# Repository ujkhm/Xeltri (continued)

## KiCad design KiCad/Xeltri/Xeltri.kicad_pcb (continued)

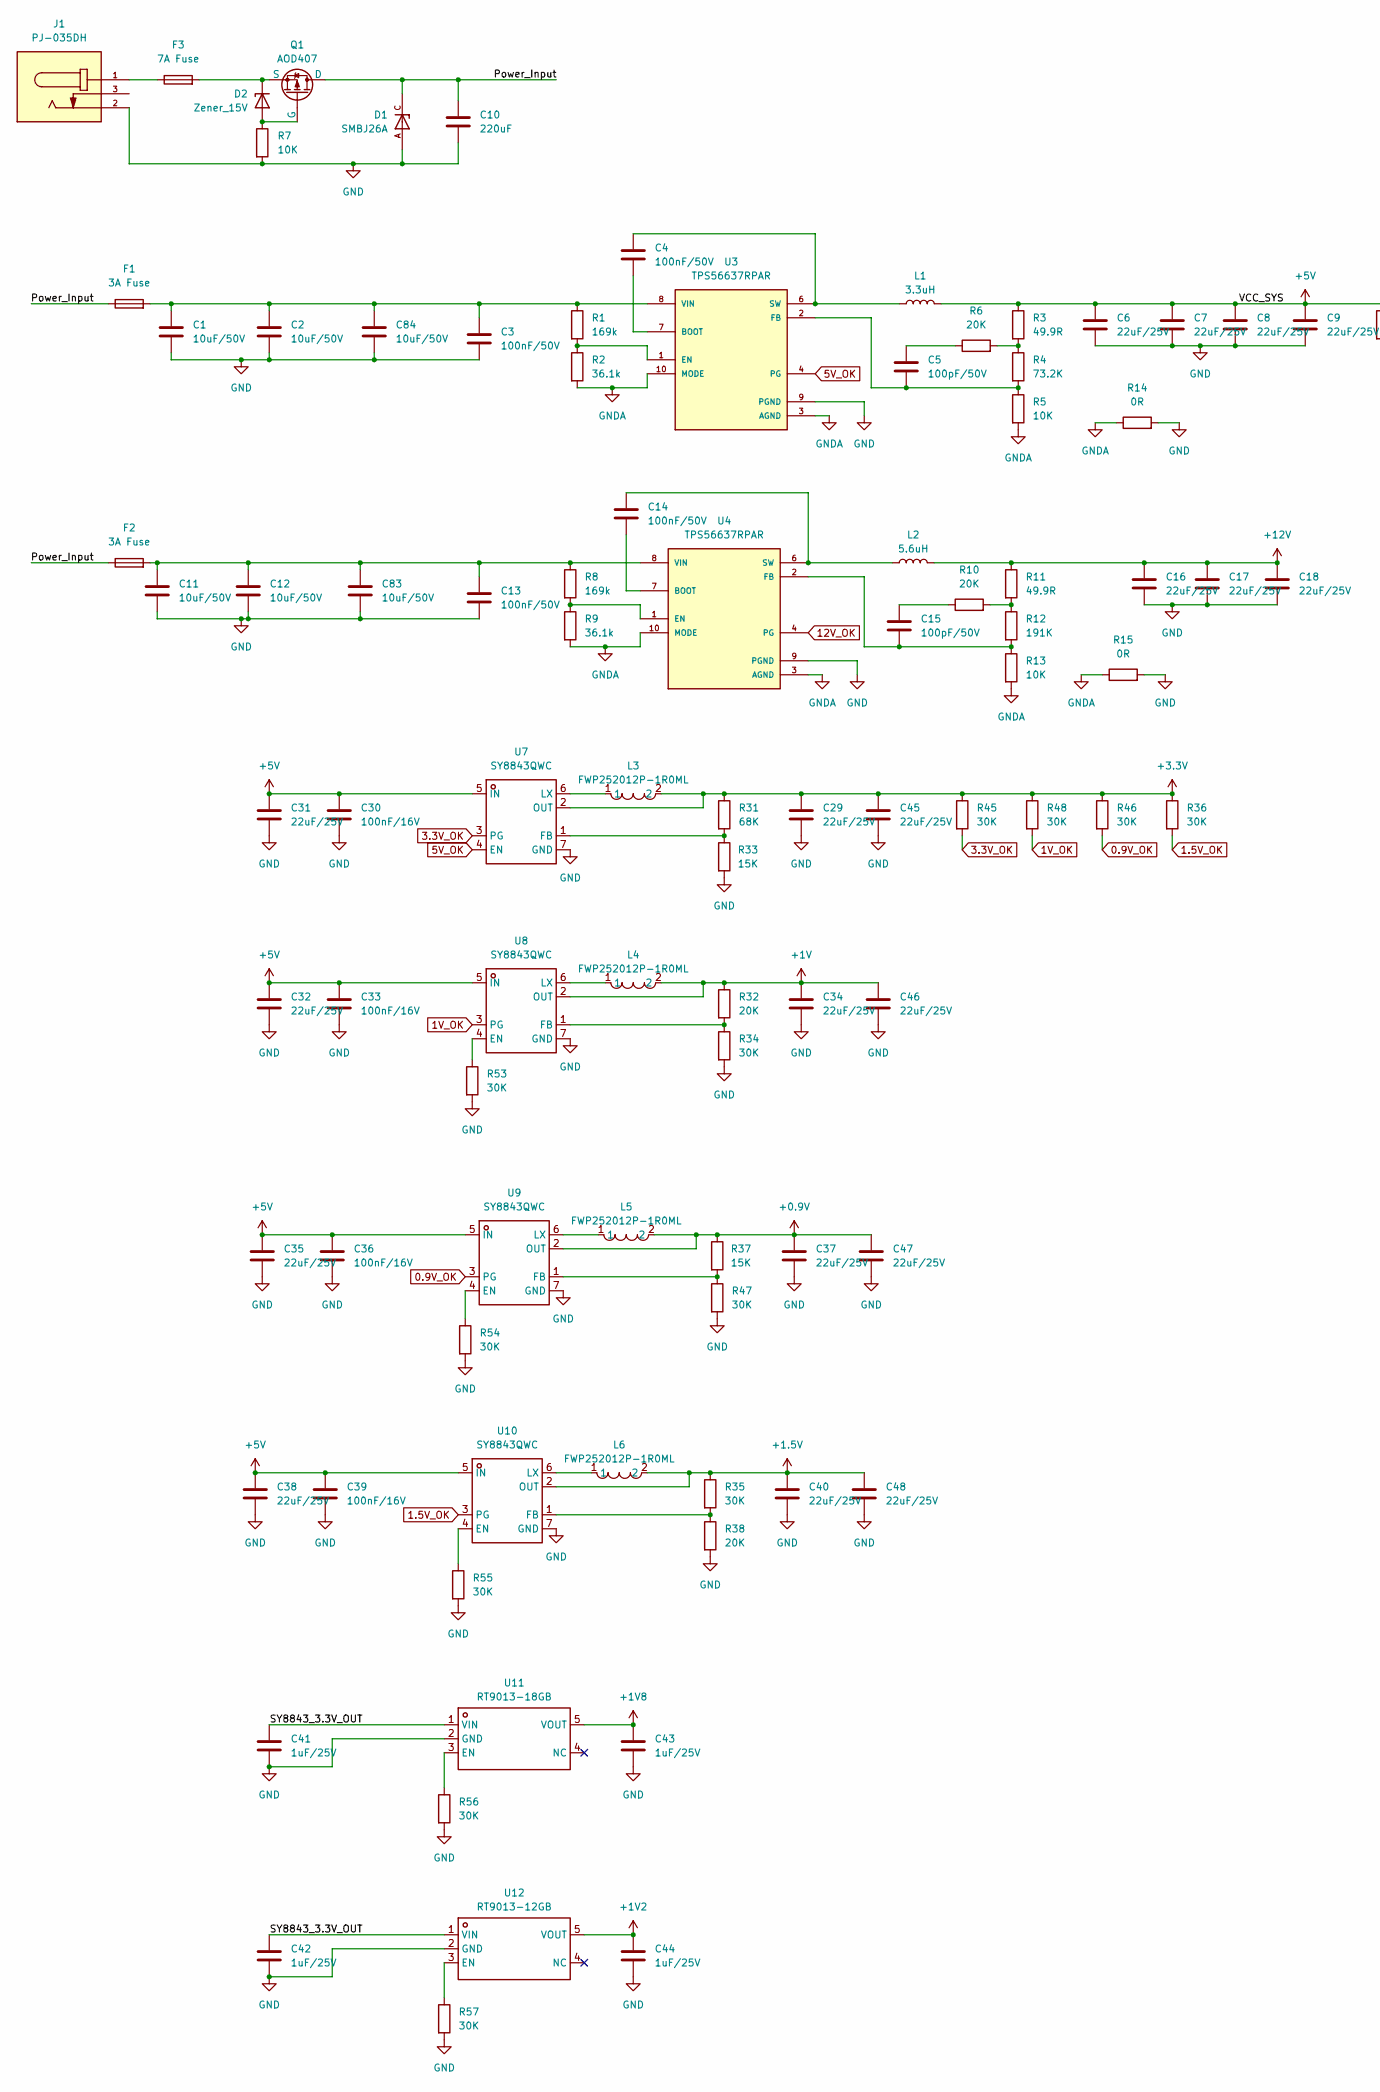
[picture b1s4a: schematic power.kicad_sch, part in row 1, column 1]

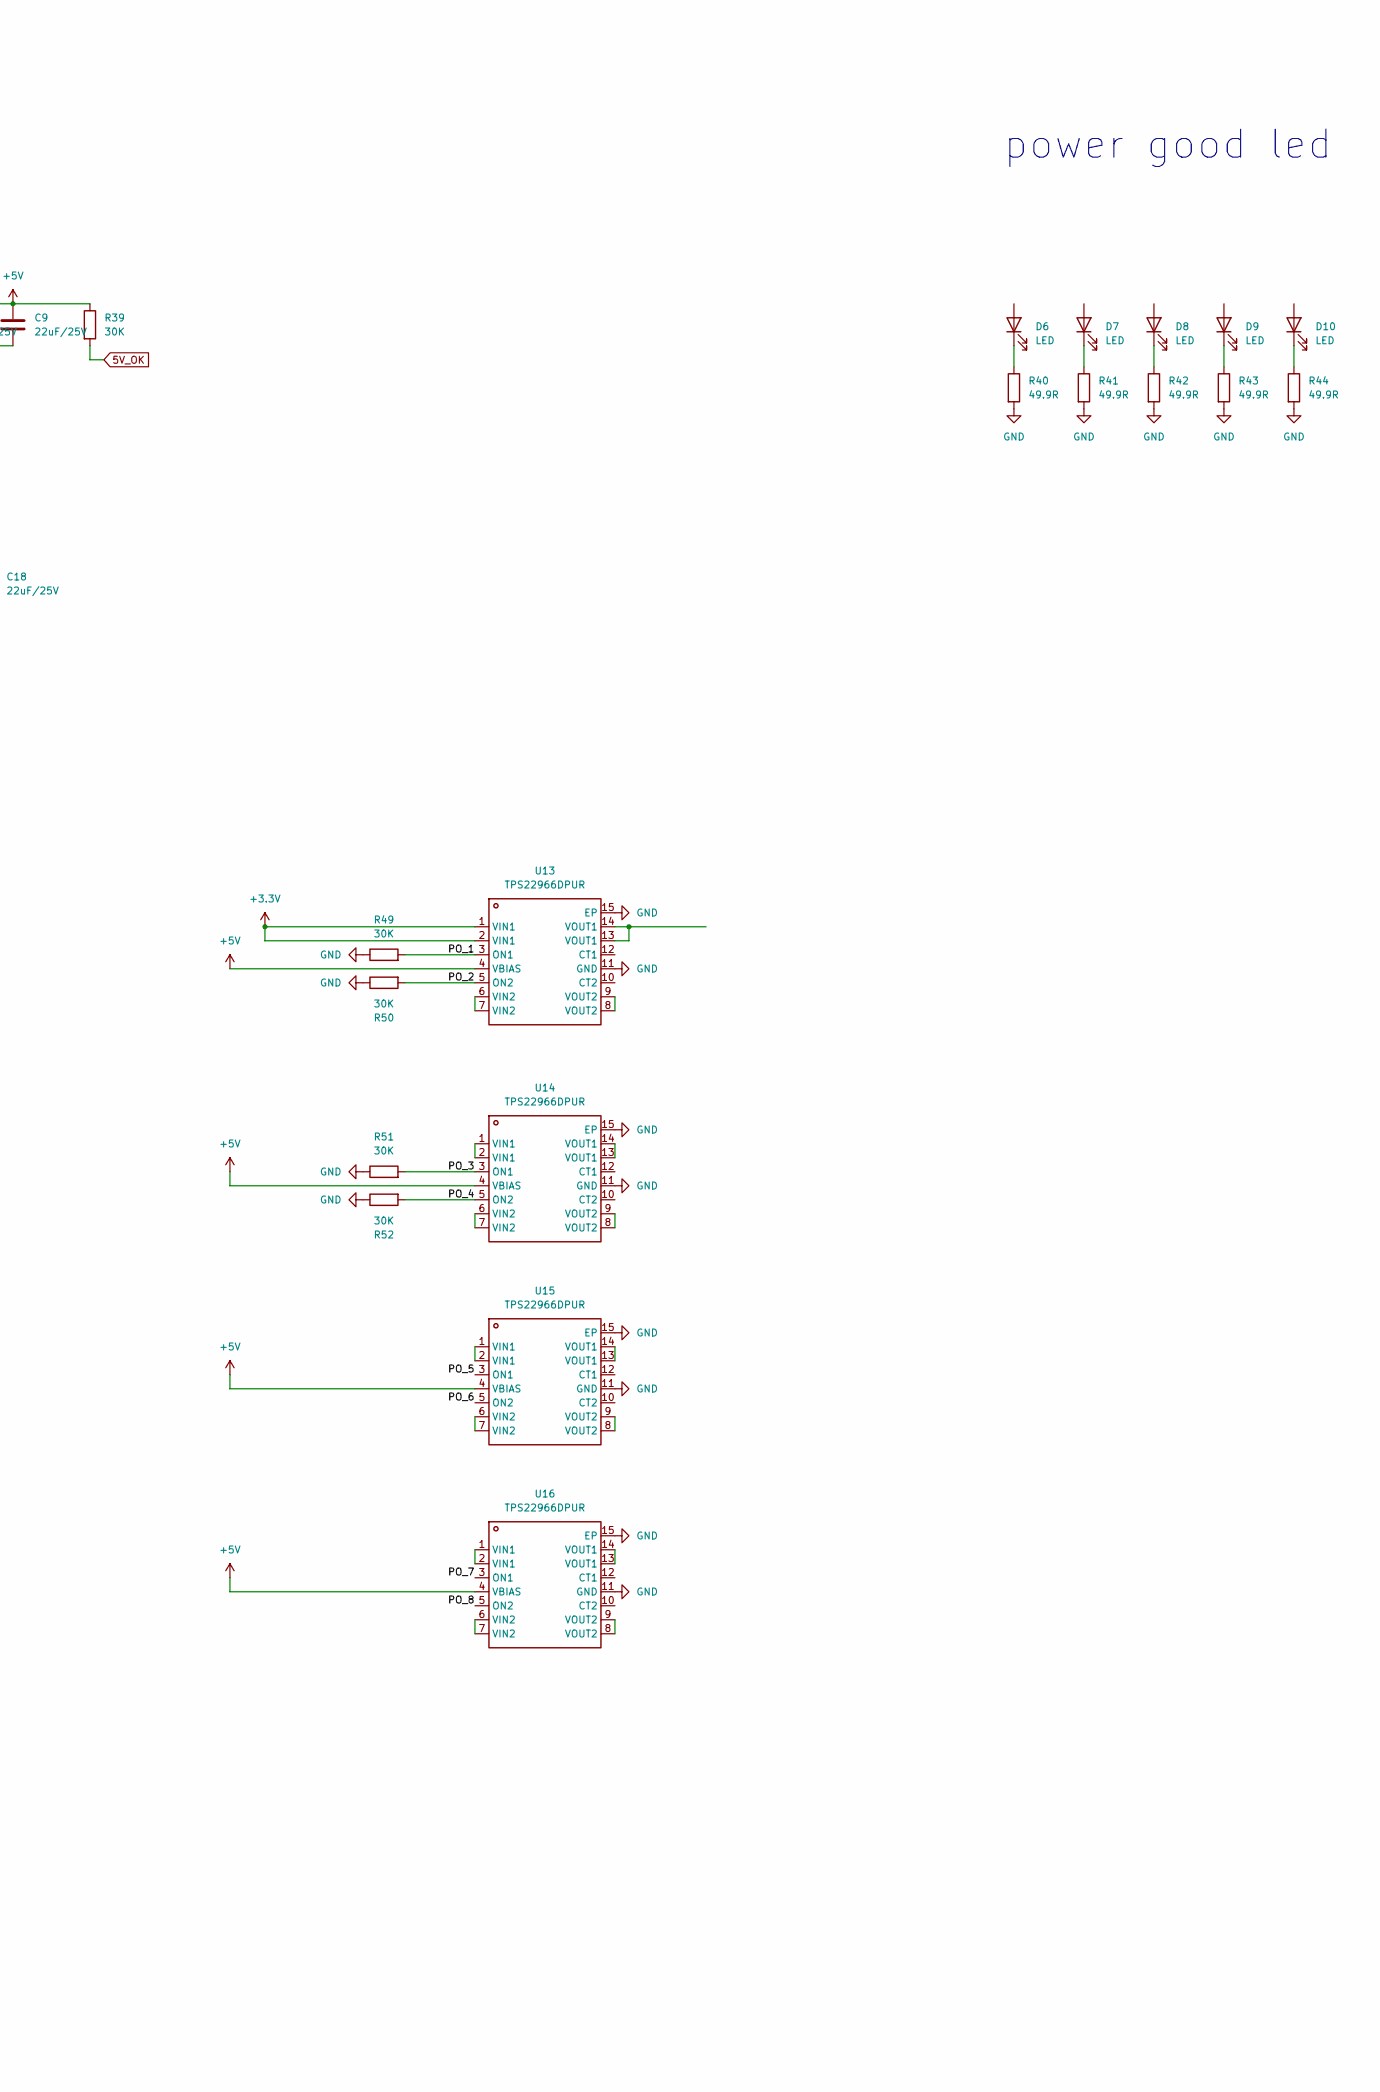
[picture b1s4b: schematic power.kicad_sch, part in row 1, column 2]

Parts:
C1, C2, C11, C12, C83, C84: 10uF/50V; C_1206_3216Metric; LCSC Part C13585
C3, C13: 100nF/50V; C_0805_2012Metric; LCSC Part C49678
C4, C14: 100nF/50V; C_0402_1005Metric; LCSC Part C307331
C5, C15: 100pF/50V; C_0402_1005Metric; LCSC Part C1546
C6, C7, C8, C9, C16, C17, C18, C29, C31, C32, C34, C35, C37, C38, C40, C45, C46, C47, C48: 22uF/25V; C_0805_2012Metric; LCSC Part C45783
C10: 220uF; C_Elec_8x10.2
C30, C33, C36, C39: 100nF/16V; C_0402_1005Metric; LCSC Part C1525
C41, C42, C43, C44: 1uF/25V; C_0402_1005Metric; LCSC Part C52923
D1: SMBJ26A; DIOM4336X265N; PARTREV F2102
D2: Zener_15V; D_SOD-123
D6, D7, D8, D9, D10: LED; LED_0603_1608Metric
F1, F2: 3A Fuse; Fuse_1206_3216Metric
F3: 7A Fuse; Fuse_1206_3216Metric
J1: PJ-035DH; CUI_PJ-035DH; PARTREV 1.05
L1: 3.3uH; L_Bourns_SRP7028A_7.3x6.6mm
L2: 5.6uH; L_Bourns_SRP7028A_7.3x6.6mm
L3, L4, L5, L6: FWP252012P-1R0ML; IND-SMD_L2.5-W2.0_YXMBL252010P; LCSC Part C5179444
Q1: AOD407; TO-252-2
R1, R8: 169k; R_0402_1005Metric
R2, R9: 36.1k; R_0402_1005Metric
R3, R11, R40, R41, R42, R43, R44: 49.9R; R_0402_1005Metric
R4: 73.2K; R_0402_1005Metric
R5, R7, R13: 10K; R_0402_1005Metric
R6, R10, R32, R38: 20K; R_0402_1005Metric
R12: 191K; R_0402_1005Metric
R14, R15: 0R; R_0402_1005Metric
R31: 68K; R_0402_1005Metric
R33, R37: 15K; R_0402_1005Metric
R34, R35, R36, R39, R45, R46, R47, R48, R49, R50, R51, R52, R53, R54, R55, R56, R57: 30K; R_0402_1005Metric
U3, U4: TPS56637RPAR; CONV_TPS56637RPAR; PARTREV A
U7, U8, U9, U10: SY8843QWC; QFN-7_L1.5-W1.5-P0.45-BL_SILERGY_SY8842QWC; LCSC Part C3151906
U11: RT9013-18GB; SOT-23-5_L3.0-W1.7-P0.95-LS2.8-BR; LCSC Part C59969
U12: RT9013-12GB; SOT-23-5_L3.0-W1.7-P0.95-LS2.8-BR; LCSC Part C58464
U13, U14, U15, U16: TPS22966DPUR; WSON-14_L3.0-W2.0-P0.40-BL-EP; LCSC Part C398913

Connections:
0.9V_OK: R46.2, U9.3 (PG)
1.5V_OK: R36.2, U10.3 (PG)
1V_OK: R48.2, U8.3 (PG)
3.3V_OK: R45.2, U7.3 (PG)
5V_OK: R39.2, U3.4 (PG), U7.4 (EN)
12V_OK: U4.4 (PG)
+0.9V: C37.1, C47.1, L5.2, R37.1, U9.2 (OUT)
+1.5V: C40.1, C48.1, L6.2, R35.1, U10.2 (OUT)
+1V: C34.1, C46.1, L4.2, R32.1, U8.2 (OUT)
+1V2: C44.1, U12.5 (VOUT)
+1V8: C43.1, U11.5 (VOUT)
+3.3V: C29.1, C45.1, L3.2, R31.1, R36.1, R45.1, R46.1, R48.1, U7.2 (OUT), U13.1 (VIN1), U13.2 (VIN1); also elsewhere on the board
+5V: C6.1, C7.1, C8.1, C9.1, C30.1, C31.1, C32.1, C33.1, C35.1, C36.1, C38.1, C39.1, L1.2, R3.1, R39.1, U7.5 (IN), U8.5 (IN), U9.5 (IN), U10.5 (IN), U13.4 (VBIAS), U14.4 (VBIAS), U15.4 (VBIAS), U16.4 (VBIAS)
+12V: C16.1, C17.1, C18.1, L2.2, R11.1; also elsewhere on the board
/power/PO_1: R49.2, U13.3 (ON1)
/power/PO_2: R50.2, U13.5 (ON2)
/power/PO_3: R51.2, U14.3 (ON1)
/power/PO_4: R52.2, U14.5 (ON2)
/power/PO_5: U15.3 (ON1)
/power/PO_6: U15.5 (ON2)
/power/PO_7: U16.3 (ON1)
/power/PO_8: U16.5 (ON2)
/power/Power_Input: C10.1, D1.C, F1.1, F2.1, Q1.1 (D)
/power/SY8843_3.3V_OUT: C41.1, C42.1, U11.1 (VIN), U12.1 (VIN)
GND: C1.2, C2.2, C3.2, C6.2, C7.2, C8.2, C9.2, C10.2, C11.2, C12.2, C13.2, C16.2, C17.2, C18.2, C29.2, C30.2, C31.2, C32.2, C33.2, C34.2, C35.2, C36.2, C37.2, C38.2, C39.2, C40.2, C41.2, C42.2, C43.2, C44.2, C45.2, C46.2, C47.2, C48.2, C83.2, C84.2, D1.A, J1.2, R7.2, R14.2, R15.2, R33.2, R34.2, R38.2, R40.2, R41.2, R42.2, R43.2, R44.2, R47.2, R49.1, R50.1, R51.1, R52.1, R53.2, R54.2, R55.2, R56.2, R57.2, U3.9 (PGND), U4.9 (PGND), U7.7 (GND), U8.7 (GND), U9.7 (GND), U10.7 (GND), U11.2 (GND), U12.2 (GND), U13.11 (GND), U13.15 (EP), U14.11 (GND), U14.15 (EP), U15.11 (GND), U15.15 (EP), U16.11 (GND), U16.15 (EP); also elsewhere on the board
GNDA: R2.2, R5.2, R9.2, R13.2, R14.1, R15.1, U3.3 (AGND), U3.10 (MODE), U4.3 (AGND), U4.10 (MODE)
unnamed: C5.1, R6.1
unnamed: C15.1, R10.1
unnamed: D2.2 (A), Q1.2 (G), R7.1
unnamed: D2.1 (K), F3.2, Q1.3 (S)
unnamed: D6.1 (K), R40.1
unnamed: D7.1 (K), R41.1
unnamed: D8.1 (K), R42.1
unnamed: D9.1 (K), R43.1
unnamed: D10.1 (K), R44.1
unnamed: F3.1, J1.1
unnamed: R3.2, R4.1, R6.2
unnamed: R10.2, R11.2, R12.1
unnamed: C4.1, U3.7 (BOOT)
unnamed: R1.2, R2.1, U3.1 (EN)
unnamed: C5.2, R4.2, R5.1, U3.2 (FB)
unnamed: C4.2, L1.1, U3.6 (SW)
unnamed: C1.1, C2.1, C3.1, C84.1, F1.2, R1.1, U3.8 (VIN)
unnamed: C14.1, U4.7 (BOOT)
unnamed: R8.2, R9.1, U4.1 (EN)
unnamed: C15.2, R12.2, R13.1, U4.2 (FB)
unnamed: C14.2, L2.1, U4.6 (SW)
unnamed: C11.1, C12.1, C13.1, C83.1, F2.2, R8.1, U4.8 (VIN)
unnamed: R31.2, R33.1, U7.1 (FB)
unnamed: L3.1, U7.6 (LX)
unnamed: R53.1, U8.4 (EN)
unnamed: R32.2, R34.1, U8.1 (FB)
unnamed: L4.1, U8.6 (LX)
unnamed: R54.1, U9.4 (EN)
unnamed: R37.2, R47.1, U9.1 (FB)
unnamed: L5.1, U9.6 (LX)
unnamed: R55.1, U10.4 (EN)
unnamed: R35.2, R38.1, U10.1 (FB)
unnamed: L6.1, U10.6 (LX)
unnamed: R56.1, U11.3 (EN)
unnamed: R57.1, U12.3 (EN)
unnamed: U13.6 (VIN2), U13.7 (VIN2)
unnamed: U13.13 (VOUT1), U13.14 (VOUT1)
unnamed: U13.8 (VOUT2), U13.9 (VOUT2)
unnamed: U14.1 (VIN1), U14.2 (VIN1)
unnamed: U14.6 (VIN2), U14.7 (VIN2)
unnamed: U14.13 (VOUT1), U14.14 (VOUT1)
unnamed: U14.8 (VOUT2), U14.9 (VOUT2)
unnamed: U15.1 (VIN1), U15.2 (VIN1)
unnamed: U15.6 (VIN2), U15.7 (VIN2)
unnamed: U15.13 (VOUT1), U15.14 (VOUT1)
unnamed: U15.8 (VOUT2), U15.9 (VOUT2)
unnamed: U16.1 (VIN1), U16.2 (VIN1)
unnamed: U16.6 (VIN2), U16.7 (VIN2)
unnamed: U16.13 (VOUT1), U16.14 (VOUT1)
unnamed: U16.8 (VOUT2), U16.9 (VOUT2)

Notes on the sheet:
power good led

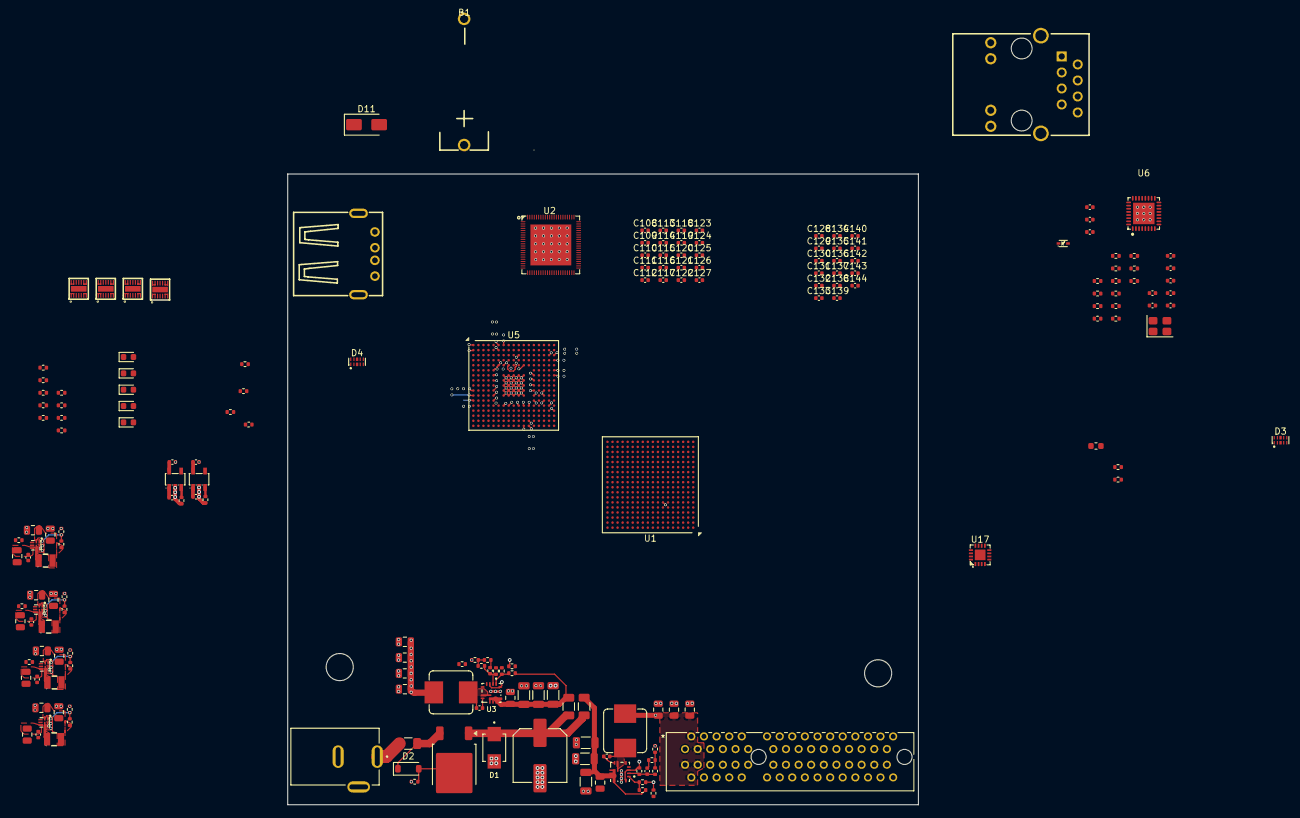
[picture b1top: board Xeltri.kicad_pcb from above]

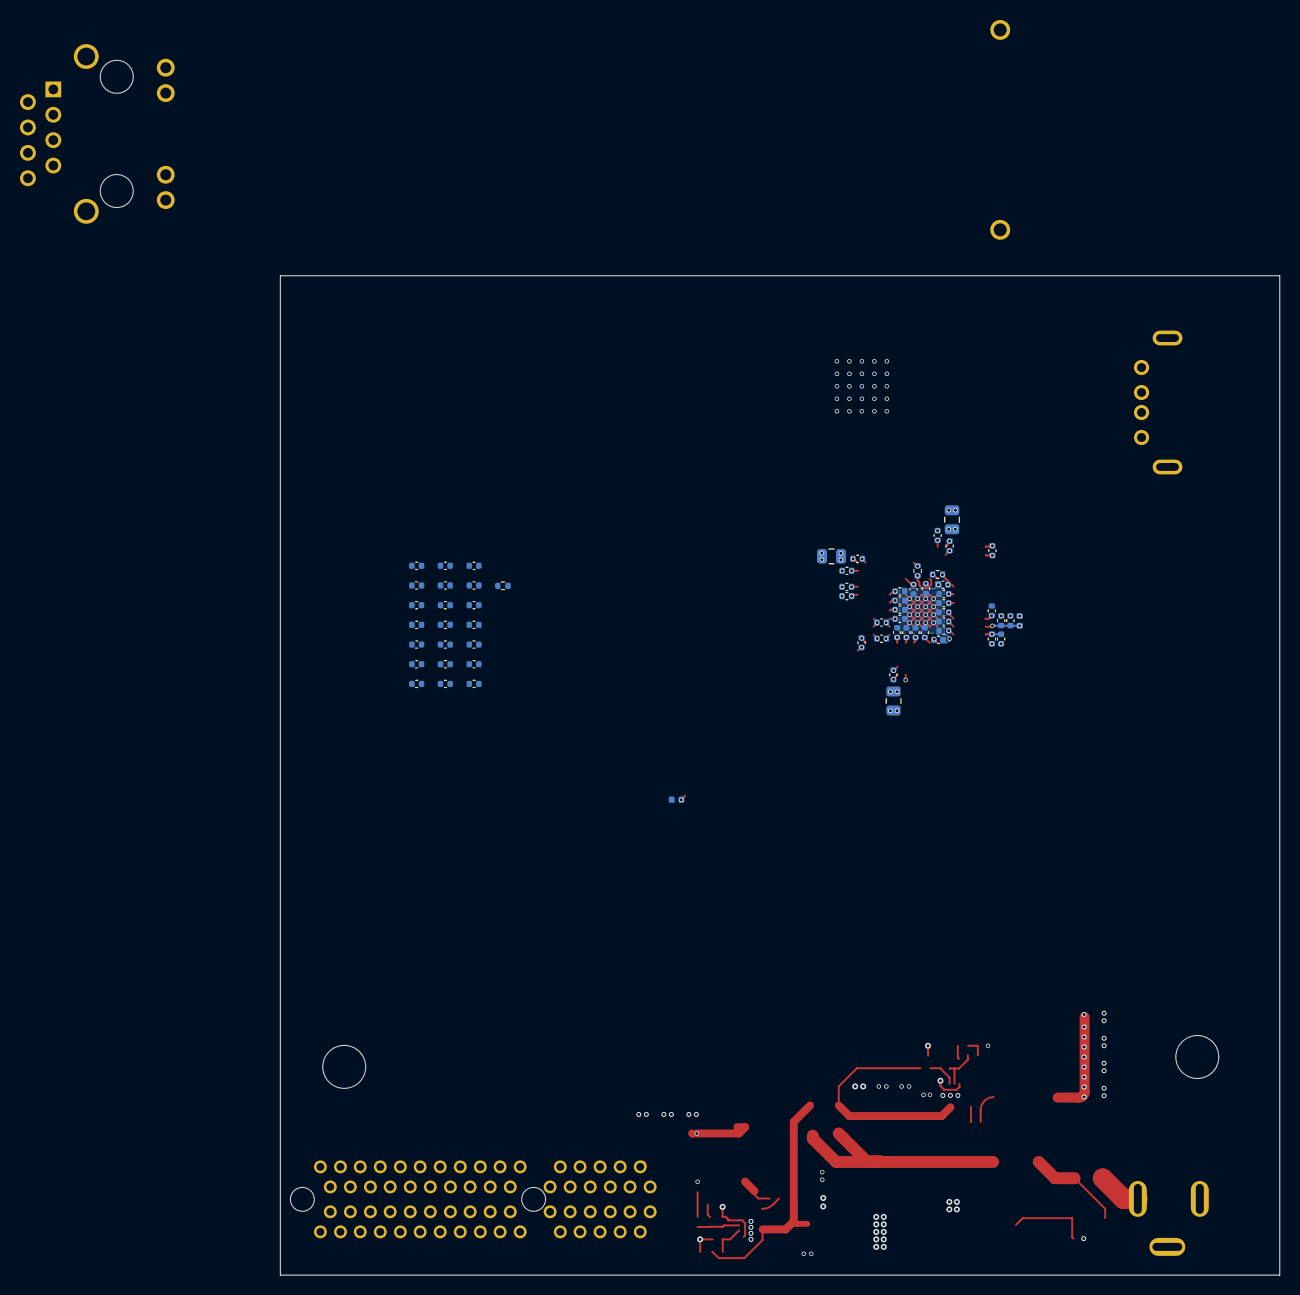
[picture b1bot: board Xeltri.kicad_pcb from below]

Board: 6 copper layers, 100.0 x 100.0 mm, 251 parts (62 on the bottom side), 113 nets.

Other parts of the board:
C19: 1nF/50V; C_0402_1005Metric
C20, C21: 10nF/50V; C_0402_1005Metric
C22, C25, C27: 100nF/16V; C_0402_1005Metric
C23, C24: 15pF/50V; C_0402_1005Metric
C26, C28: 10uF/6.3V; C_0402_1005Metric
D3, D4: ESD224DQAR; USON-10_L2.5-W1.0-P0.50-BL
D5: LESD5D5.0CT1G; SOD-523_L1.2-W0.8-LS1.6-BI
FB1: 220R@100M; L_0603_1608Metric
J2: 877159106; CONN_87715-9106_MOL
J3: HR911105A_C12074; RJ45-TH_HR911105A
R16, R17: 510R; R_0402_1005Metric
R18, R21, R22, R23, R29, R30: 4.7k; R_0402_1005Metric
R19, R20: 1.5k; R_0402_1005Metric
R24: 2.49k; R_0402_1005Metric
R25, R26, R27, R28: 22R; R_0402_1005Metric
U6: RTL8201F-VB-CG; QFN-32_L5.0-W5.0-P0.50-BL-EP3.4
U17: CH334P; QFN-16_L3.0-W3.0-P0.50-BL-EP1.7
USB1: AF 90° ZJDG ZB; USB-A-TH_AF-90-ZJDG-ZB
Y1: 25Mhz; Crystal_SMD_3225-4Pin_3.2x2.5mm

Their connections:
+12V: J2.A2, J2.A3, J2.B1, J2.B2, J2.B3; also elsewhere on the board
/Expansion_Port/ETH_RX_N: J3.6 (RD-), R28.1
/Expansion_Port/ETH_RX_P: J3.3 (RD+), R27.1
/Expansion_Port/ETH_TX_N: J3.2 (TD-), R26.1
/Expansion_Port/ETH_TX_P: J3.1 (TD+), R25.1
/Expansion_Port/LED_ACT: R16.1, R18.1, U6.24 (LED0/PHYAD[0]/PMEB)
/Expansion_Port/LED_LINK: R17.1, R23.1, U6.25 (LED1/PHYAD[1])
Ethernet_3V3: C26.1, C27.1, C28.1, J3.9, R18.2, R19.2, R20.2, R21.2, R29.1, U6.7 (AVDD33), U6.14 (DVDD33), U6.30 (AVDD33)
GND: C19.1, C20.1, C21.1, C22.2, C23.1, C24.1, C25.1, C26.2, C27.2, C28.2, D5.1, FB1.2, J2.A4, J2.B4, J3.11, R22.2, R23.2, R24.1, R30.1, U6.33 (EP), Y1.2 (G), Y1.4 (G); also elsewhere on the board
unnamed: C20.2, J3.4
unnamed: C21.2, J3.5
unnamed: FB1.1, J3.SH1, J3.SH2
unnamed: C19.2, D5.2, J3.8 (CHSGND)
unnamed: J3.10, R16.2
unnamed: J3.12, R17.2
unnamed: C25.2, U6.2 (AVDD10OUT)
unnamed: C24.2, U6.31 (CKXTAL1), Y1.1
unnamed: C23.2, U6.32 (CKXTAL2), Y1.3
unnamed: C22.1, U6.29 (DVDD10OUT)
unnamed: R25.2, U6.3 (MDI+[0])
unnamed: R27.2, U6.5 (MDI+[1])
unnamed: R26.2, U6.4 (MDI-[0])
unnamed: R28.2, U6.6 (MDI-[1])
unnamed: R24.2, U6.1 (RSET)
unnamed: R29.2, U6.8 (RXDV)
PHY_MDC: R20.1, U6.22 (MDC)
PHY_MDIO: R19.1, U6.23 (MDIO)
PHY_RSTN: R21.1, U6.21 (PHYRSTB)
PHY_RXD1: R30.2, U6.10 (RXD[1])
PHY_RXER: R22.1, U6.28 (RXER/FXEN)
